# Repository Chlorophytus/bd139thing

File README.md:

# bd139thing

The BD139 Thing is a 300mW RMS stereo Hi-Fi Class-A amplifier.

It is pairable with a set of very high sensitivity (>90dB) speakers for audio playback.

Distortion analysis has not been done yet, but [THD][total-harmonic-distortion]/[IMD][intermodulation-distortion] is probably 5-10%; most of it is pleasing "tube sound like" distortion, transistorized.

## Current state

I am working on another revision of the design.
The BD139 cascode is modular, meaning it can have many in parallel when paired with a suitable power supply and power filtering capacitors.
Heat dissipation on the negative feedback shunts and power delivery are primary concerns.

[total-harmonic-distortion]: https://en.wikipedia.org/wiki/Total_harmonic_distortion
[intermodulation-distortion]: https://en.wikipedia.org/wiki/Intermodulation

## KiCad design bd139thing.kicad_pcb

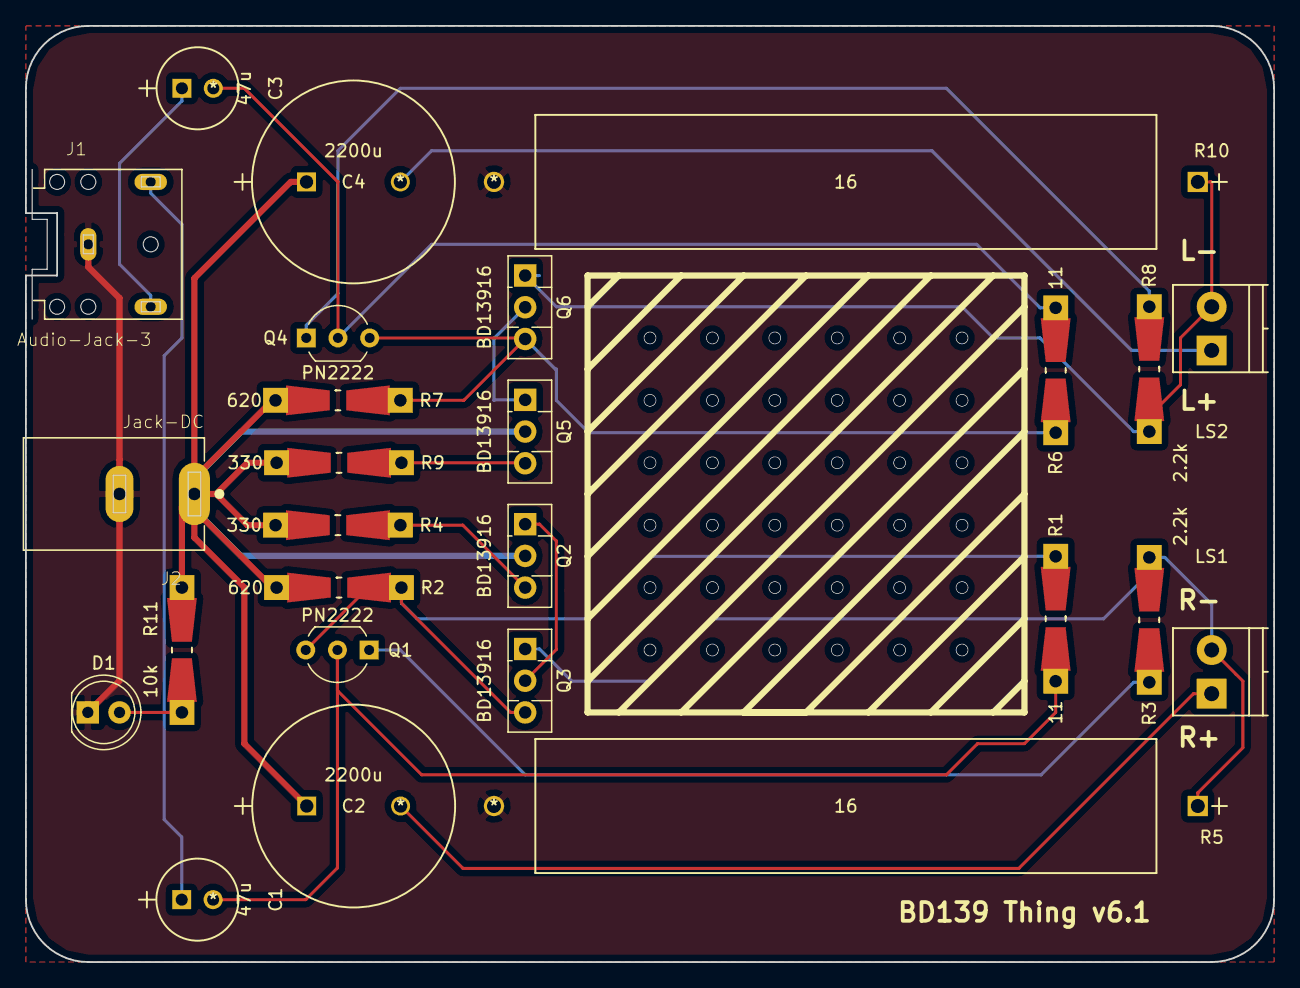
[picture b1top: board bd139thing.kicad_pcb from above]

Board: 2 copper layers, 100.0 x 75.0 mm, 26 parts (0 on the bottom side), 19 nets.

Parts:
C1, C3: 47u; ECA-1HHG470
C2, C4: 2200u; ECA-1HHG222
D1: LED; LED_D5.0mm
J1: Audio-Jack-3; CUI_SJ1-3523NG
J2: Jack-DC; CUI_PJ-037A
LS1: L; TerminalBlock_Pheonix_PT-3.5mm_2pol
LS2: R; TerminalBlock_Pheonix_PT-3.5mm_2pol
Q1, Q4: PN2222; TO-92_Inline_Wide
Q2, Q3, Q5, Q6: BD13916; TO-126_Vertical
R1, R6: 11; Resistor_SMD+THTuniversal_0805to1206_RM10_HandSoldering
R2, R7: 620; Resistor_SMD+THTuniversal_0805to1206_RM10_HandSoldering
R3, R8: 2.2k; Resistor_SMD+THTuniversal_0805to1206_RM10_HandSoldering
R4, R9: 330; Resistor_SMD+THTuniversal_0805to1206_RM10_HandSoldering
R5, R10: 16; SQP10AJB-16R
R11: 10k; Resistor_SMD+THTuniversal_0805to1206_RM10_HandSoldering

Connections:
+12V: C2.1, C4.1, J2.1, Q2.2, Q5.2, R2.1, R4.1, R7.1, R9.1, R11.2
GND: D1.1, J1.1, J2.2, R5.2, R10.2
unnamed: C1.1, J1.3
unnamed: C1.2, Q1.2, R1.2
unnamed: C2.2, LS1.1
unnamed: C3.1, J1.2
unnamed: C3.2, Q4.2, R6.2
unnamed: C4.2, LS2.1
unnamed: D1.2, R11.1
unnamed: LS1.2, Q3.1, R3.2, R5.1
unnamed: LS2.2, Q6.1, R8.2, R10.1
unnamed: Q1.1, R3.1
unnamed: Q1.3, Q3.3, R1.1, R2.2
unnamed: Q2.1, Q3.2
unnamed: Q2.3, R4.2
unnamed: Q4.1, R8.1
unnamed: Q4.3, Q6.3, R6.1, R7.2
unnamed: Q5.1, Q6.2
unnamed: Q5.3, R9.2

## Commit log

2019-07-19 add initial r4p0 ok
2019-07-22 r5p0 ok, improved placement on 75x75mm
2019-07-26 prepare fixes p1
2019-07-26 correct problems thx ok r5p2
2019-08-04 6 ok
2019-08-06 ahgod if you know what happened you wouldn't be happy
2019-08-17 design wasn't performing as planned
2019-12-03 Create LICENSE
2021-12-08 Update README
    I have some more information to give.
2021-12-08 New symbols for simulating are in

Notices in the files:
parts and their libraries:
Copyright 2016 Accelerated Designs. All rights reserved.
